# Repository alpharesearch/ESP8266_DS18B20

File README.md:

# ESP8266_DS18B20

Most parts are optional, this is just a little breakout board for the esp8266. I just used parts that I had already at home. With the little prototyping area it allows to add different little projects. For example I have a some boards connected to Smartthings hub. Right now I'm using 3 versions: log 5 temperatures, red and green status LED, press two buttons on bed remote control.

https://htmlpreview.github.io/?https://github.com/alpharesearch/ESP8266_DS18B20/blob/master/esp8266/bom/ibom.html

Here is the string for "Formatted row" at the IFTTT recipe I use:

=TIMEVALUE(SUBSTITUTE("{{OccurredAt}}"," at ", " ")) + DATEVALUE(SUBSTITUTE("{{OccurredAt}}"," at ", " "))||| {{EventName}} ||| {{Value1}} |||{{Value2}} ||| {{Value3}}|||={{Value3}}*9/5+32|||=IF("{{Value1}}"="40:255:148:214:68:22:3", "clean to inside", "")& IF("{{Value1}}"="40:255:252:69:80:22:4", "water heater room", "")& IF("{{Value1}}"="40:255:229:240:68:22:3", "dirty inside", "")&IF("{{Value1}}"="40:255:111:38:80:22:4", "clean from outside", "")&IF("{{Value1}}"="40:255:95:255:68:22:3", "dirty to outside", "")

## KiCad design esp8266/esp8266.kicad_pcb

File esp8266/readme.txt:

I had to merge both the drl files via gerbv to excellio file...
renamed the edge cuts to gml extension

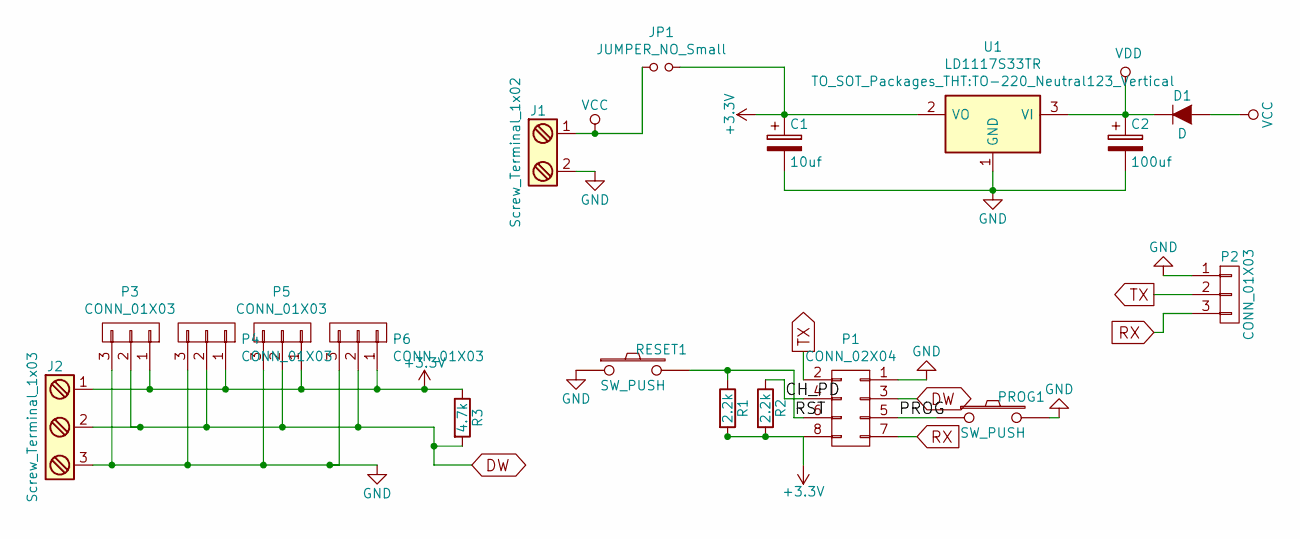
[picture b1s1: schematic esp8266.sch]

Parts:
C1: 10uf; C_Radial_D5_L6_P2.5
C2: 100uf; C_Radial_D8_L11.5_P3.5
D1: D; Diode_DO-41_SOD81_Horizontal_RM10
J1: Screw_Terminal_1x02; bornier2
J2: Screw_Terminal_1x03; bornier3
JP1: JUMPER_NO_Small; TEST_POINT_2PADS
P1: CONN_02X04; Socket_Strip_Straight_2x04
P2: CONN_01X03; Pin_Header_Straight_1x03
P3, P4, P5, P6: CONN_01X03; Socket_Strip_Straight_1x03
PROG1: SW_PUSH; SW_PUSH_6mm
R1, R2: 2.2k; Resistor_Horizontal_RM10mm
R3: 4.7k; Resistor_Horizontal_RM10mm
RESET1: SW_PUSH; SW_PUSH_6mm
U1: LD1117S33TR; TO-220_Neutral123_Vertical

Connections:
+3V3: C1.1, J2.1, JP1.2, P1.8, P3.1, P4.1, P5.1, P6.1, R1.2, R2.2, R3.1, U1.2 (VO)
/CH_PD: P1.4, R2.1
/PROG: P1.5, PROG1.1
/RST: P1.6, R1.1, RESET1.2
DW: J2.2, P1.3, P3.2, P4.2, P5.2, P6.2, R3.2
GND: C1.2, C2.2, J1.2, J2.3, P1.1, P2.1, P3.3, P4.3, P5.3, P6.3, PROG1.2, RESET1.1, U1.1 (GND)
RX: P1.7, P2.3
TX: P1.2, P2.2
VCC: D1.2 (A), J1.1, JP1.1
VDD: C2.1, D1.1 (K), U1.3 (VI)

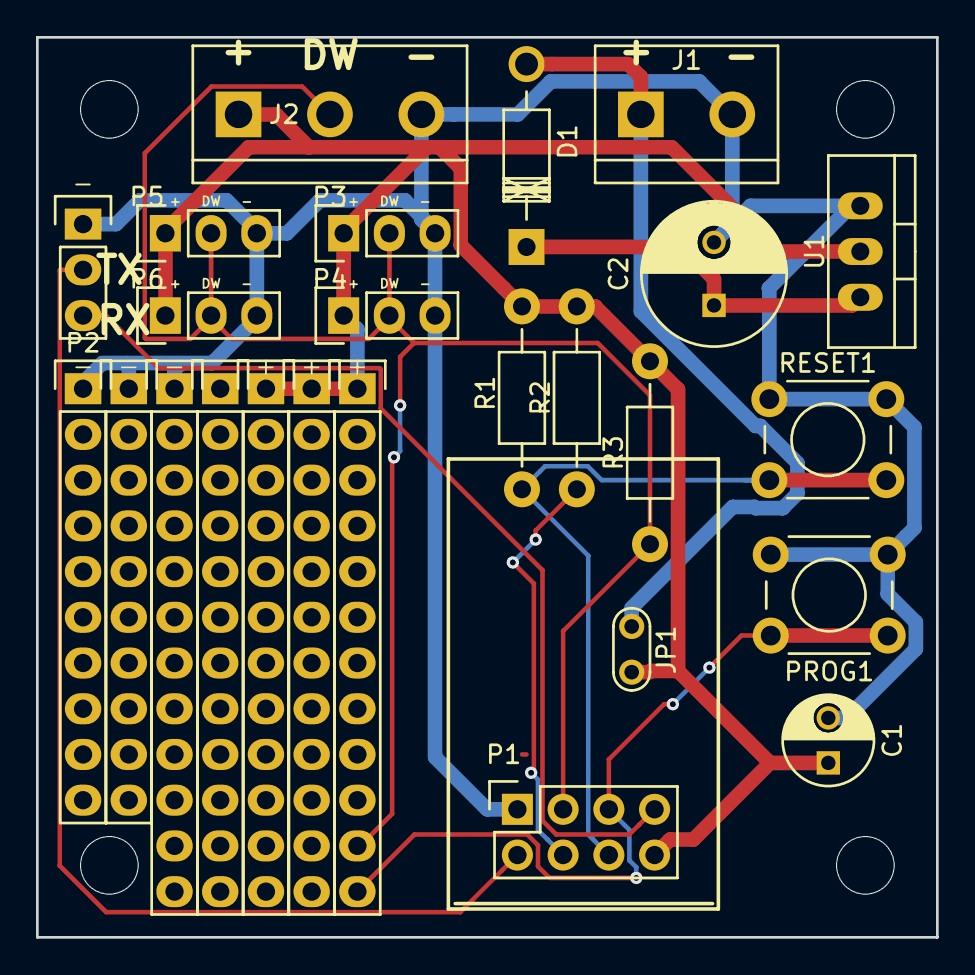
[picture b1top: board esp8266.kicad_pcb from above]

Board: 2 copper layers, 50.0 x 50.0 mm, 18 parts (0 on the bottom side), 10 nets.

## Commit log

2016-11-12 changed to LD1117
2016-11-12 get some errors DRC corrected
2016-11-12 arduino IDE needs this folder
2016-11-13 add component description to back silk
2016-11-14 try to add switch to 3d view
2017-02-03 add C3
2017-02-03 fix for dri
2018-11-18 interactive html bom
2019-02-14 kicad 5
